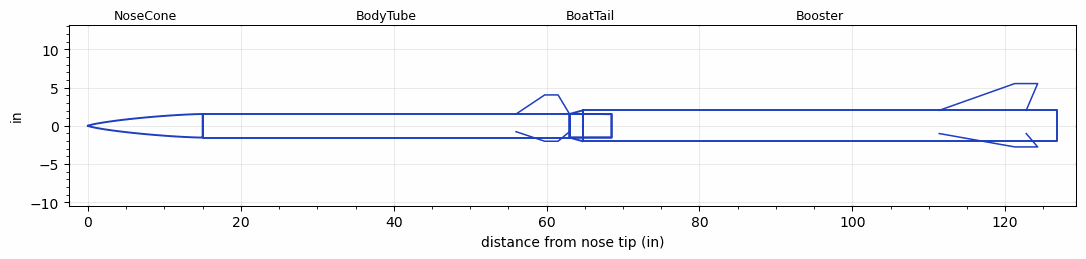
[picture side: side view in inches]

<RASAeroDocument>
 <FileVersion>2</FileVersion>
 <RocketDesign>
  <NoseCone>
   <Length>15</Length>
   <Diameter>3.08</Diameter>
   <Shape>Von Karman Ogive</Shape>
   <Location>0</Location>
  </NoseCone>
  <BodyTube>
   <Length>48</Length>
   <Diameter>3.08</Diameter>
   <Location>15</Location>
   <BoattailLength>5.5</BoattailLength>
   <BoattailRearDiameter>3.07</BoattailRearDiameter>
   <Fin>
    <Count>3</Count>
    <Chord>7</Chord>
    <Span>2.5</Span>
    <SweepDistance>3.75</SweepDistance>
    <TipChord>1.75</TipChord>
    <Thickness>0.125</Thickness>
    <Location>7</Location>
    <AirfoilSection>Hexagonal</AirfoilSection>
    <FX1>0.5</FX1>
    <FX3>0.5</FX3>
   </Fin>
  </BodyTube>
  <BoatTail>
   <Length>5.5</Length>
   <Diameter>3.08</Diameter>
   <RearDiameter>3.07</RearDiameter>
   <Location>63</Location>
  </BoatTail>
  <Booster>
   <Length>62</Length>
   <Diameter>4.05</Diameter>
   <InsideDiameter>3.08</InsideDiameter>
   <LaunchShoeArea>0.0331</LaunchShoeArea>
   <Location>63</Location>
   <ShoulderLength>1.75</ShoulderLength>
   <Fin>
    <Count>3</Count>
    <Chord>11.375</Chord>
    <Span>3.5</Span>
    <SweepDistance>9.875</SweepDistance>
    <TipChord>3</TipChord>
    <Thickness>0.1875</Thickness>
    <Location>15.375</Location>
    <AirfoilSection>Hexagonal</AirfoilSection>
    <FX1>0.5</FX1>
    <FX3>0.5</FX3>
   </Fin>
  </Booster>
  <Surface>Rough Camouflage Paint</Surface>
  <ModifiedBarrowman>False</ModifiedBarrowman>
  <Turbulence>True</Turbulence>
  <SustainerNozzle>1.23</SustainerNozzle>
  <Booster1Nozzle>1.75</Booster1Nozzle>
  <UseBooster1>True</UseBooster1>
  <UseBooster2>False</UseBooster2>
  <Comments>AeroPac 104K Carmack Prize Rocket
Black Rock Launch Site

GPS Altitude
Altitude = 104659 ft

Apogee 17.1 miles downrange.

RASAero II Prediction = 113786 ft
Error = 8.72%
</Comments>
 </RocketDesign>
 <LaunchSite>
  <Altitude>3750</Altitude>
  <Pressure>0</Pressure>
  <RodAngle>7.64</RodAngle>
  <RodLength>12</RodLength>
  <Temperature>80</Temperature>
  <WindSpeed>0</WindSpeed>
 </LaunchSite>
 <Recovery>
  <Altitude1>1000</Altitude1>
  <Altitude2>1000</Altitude2>
  <DeviceType1>Parachute</DeviceType1>
  <DeviceType2>None</DeviceType2>
  <Event1>False</Event1>
  <Event2>False</Event2>
  <Size1>36</Size1>
  <Size2>1</Size2>
  <EventType1>None</EventType1>
  <EventType2>None</EventType2>
  <CD1>1.33</CD1>
  <CD2>1.33</CD2>
 </Recovery>
 <SimulationList>
  <Simulation>
   <SustainerEngine>M685W-Proto  (AT)</SustainerEngine>
   <SustainerLaunchWt>22.79</SustainerLaunchWt>
   <SustainerNozzleDiameter>1.23</SustainerNozzleDiameter>
   <SustainerCG>37.9</SustainerCG>
   <SustainerIgnitionDelay>6</SustainerIgnitionDelay>
   <Booster1Engine>N1048  (AT)</Booster1Engine>
   <Booster1LaunchWt>61</Booster1LaunchWt>
   <Booster1SeparationDelay>0</Booster1SeparationDelay>
   <Booster1IgnitionDelay>0</Booster1IgnitionDelay>
   <Booster1CG>77.5</Booster1CG>
   <Booster1NozzleDiameter>1.75</Booster1NozzleDiameter>
   <IncludeBooster1>True</IncludeBooster1>
   <Booster2Delay>0</Booster2Delay>
   <IncludeBooster2>False</IncludeBooster2>
   <TimetoApogee>98.33942</TimetoApogee>
   <MaxAltitude>113786.4</MaxAltitude>
   <MaxVelocity>3125.964</MaxVelocity>
  </Simulation>
 </SimulationList>
</RASAeroDocument>
